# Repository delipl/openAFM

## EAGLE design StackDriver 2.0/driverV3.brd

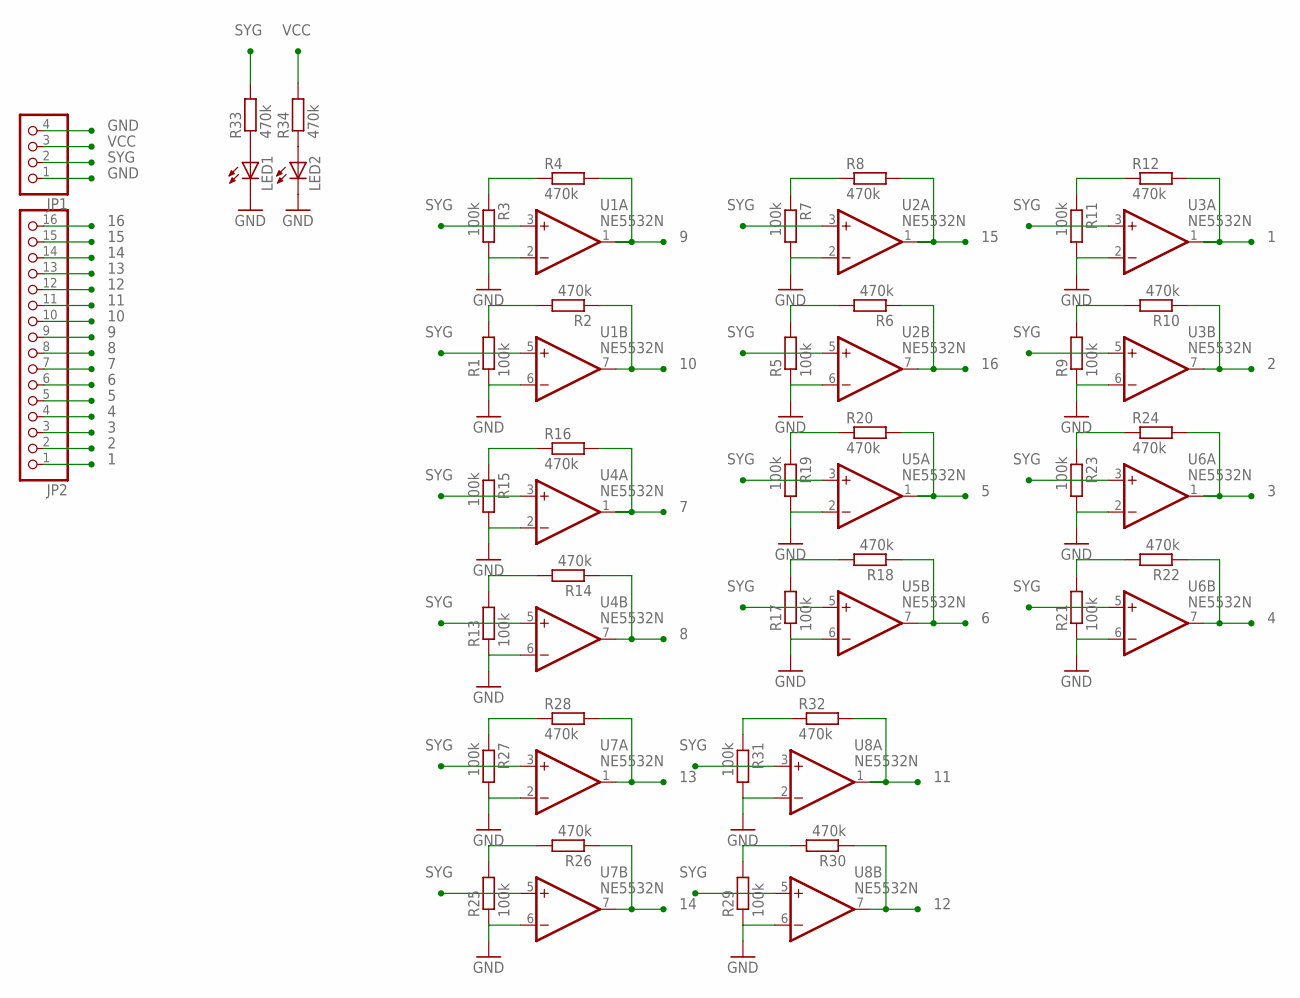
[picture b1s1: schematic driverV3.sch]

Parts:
JP1: PINHD-1X4; 1X04
JP2: PINHD-1X16; 1X16
LED1, LED2: LED_ELD260; LED_LD260
R1, R3, R5, R7, R9, R11, R13, R15, R17, R19, R21, R23, R25, R27, R29, R31: 100k; 0204/7
R2, R4, R6, R8, R10, R12, R14, R16, R18, R20, R22, R24, R26, R28, R30, R32, R33, R34: 470k; 0204/7
U1, U2, U3, U4, U5, U6, U7, U8: NE5532N; DIL08

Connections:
1: JP2.1, R12.2, U3.1 (OUT)
2: JP2.2, R10.1, U3.7 (OUT)
3: JP2.3, R24.2, U6.1 (OUT)
4: JP2.4, R22.1, U6.7 (OUT)
5: JP2.5, R20.2, U5.1 (OUT)
6: JP2.6, R18.1, U5.7 (OUT)
7: JP2.7, R16.2, U4.1 (OUT)
8: JP2.8, R14.1, U4.7 (OUT)
9: JP2.9, R4.2, U1.1 (OUT)
10: JP2.10, R2.1, U1.7 (OUT)
11: JP2.11, R32.2, U8.1 (OUT)
12: JP2.12, R30.1, U8.7 (OUT)
13: JP2.13, R28.2, U7.1 (OUT)
14: JP2.14, R26.1, U7.7 (OUT)
15: JP2.15, R8.2, U2.1 (OUT)
16: JP2.16, R6.1, U2.7 (OUT)
GND: JP1.1, JP1.4, LED1.K (C), LED2.K (C), R1.1, R3.2, R5.1, R7.2, R9.1, R11.2, R13.1, R15.2, R17.1, R19.2, R21.1, R23.2, R25.1, R27.2, R29.1, R31.2, U1.2 (-IN), U1.4 (V-), U1.6 (-IN), U2.2 (-IN), U2.4 (V-), U2.6 (-IN), U3.2 (-IN), U3.4 (V-), U3.6 (-IN), U4.2 (-IN), U4.4 (V-), U4.6 (-IN), U5.2 (-IN), U5.4 (V-), U5.6 (-IN), U6.2 (-IN), U6.4 (V-), U6.6 (-IN), U7.2 (-IN), U7.4 (V-), U7.6 (-IN), U8.2 (-IN), U8.4 (V-), U8.6 (-IN)
unnamed: R5.2, R6.2
unnamed: R1.2, R2.2
unnamed: R7.1, R8.1
unnamed: R9.2, R10.2
unnamed: R3.1, R4.1
unnamed: R11.1, R12.1
unnamed: R13.2, R14.2
unnamed: R15.1, R16.1
unnamed: R17.2, R18.2
unnamed: R19.1, R20.1
unnamed: R21.2, R22.2
unnamed: R23.1, R24.1
unnamed: R25.2, R26.2
unnamed: R27.1, R28.1
unnamed: R29.2, R30.2
unnamed: R31.1, R32.1
unnamed: LED1.A, R33.1
unnamed: LED2.A, R34.1
SYG: JP1.2, R33.2, U1.3 (+IN), U1.5 (+IN), U2.3 (+IN), U2.5 (+IN), U3.3 (+IN), U3.5 (+IN), U4.3 (+IN), U4.5 (+IN), U5.3 (+IN), U5.5 (+IN), U6.3 (+IN), U6.5 (+IN), U7.3 (+IN), U7.5 (+IN), U8.3 (+IN), U8.5 (+IN)
VCC: JP1.3, R34.2, U1.8 (V+), U2.8 (V+), U3.8 (V+), U4.8 (V+), U5.8 (V+), U6.8 (V+), U7.8 (V+), U8.8 (V+)

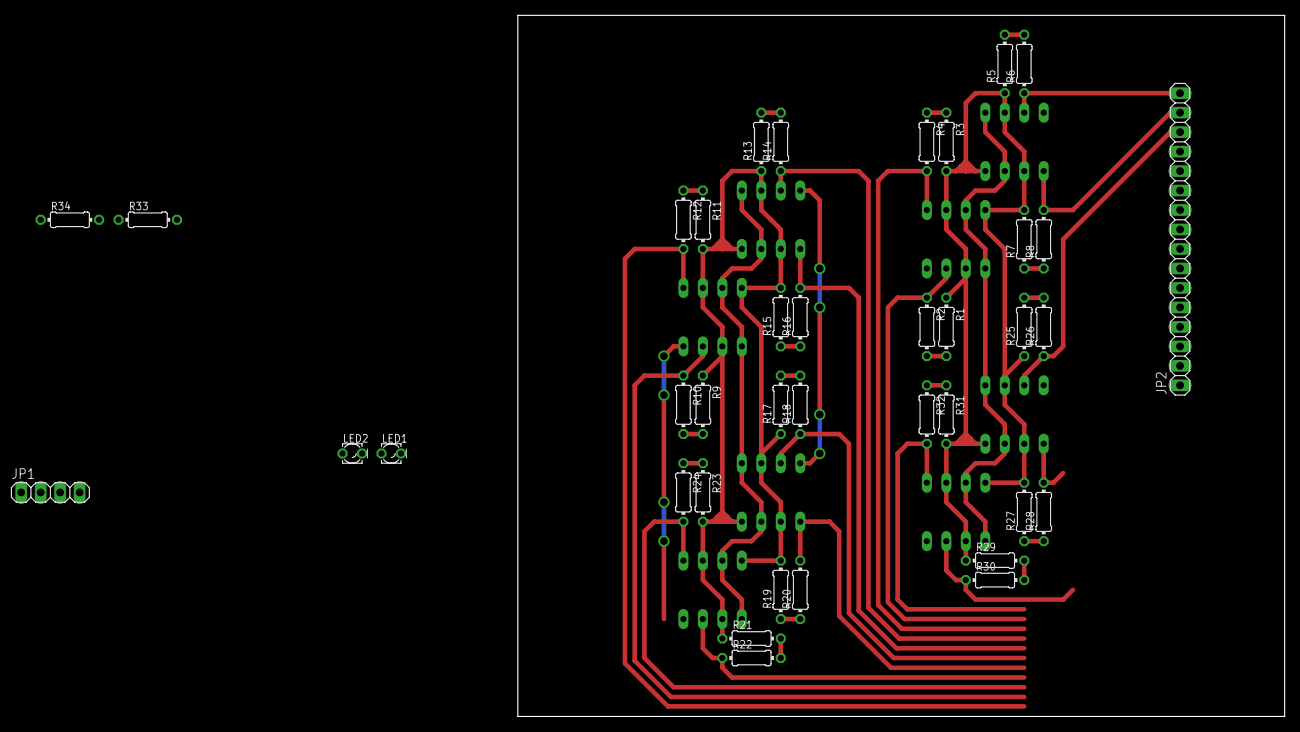
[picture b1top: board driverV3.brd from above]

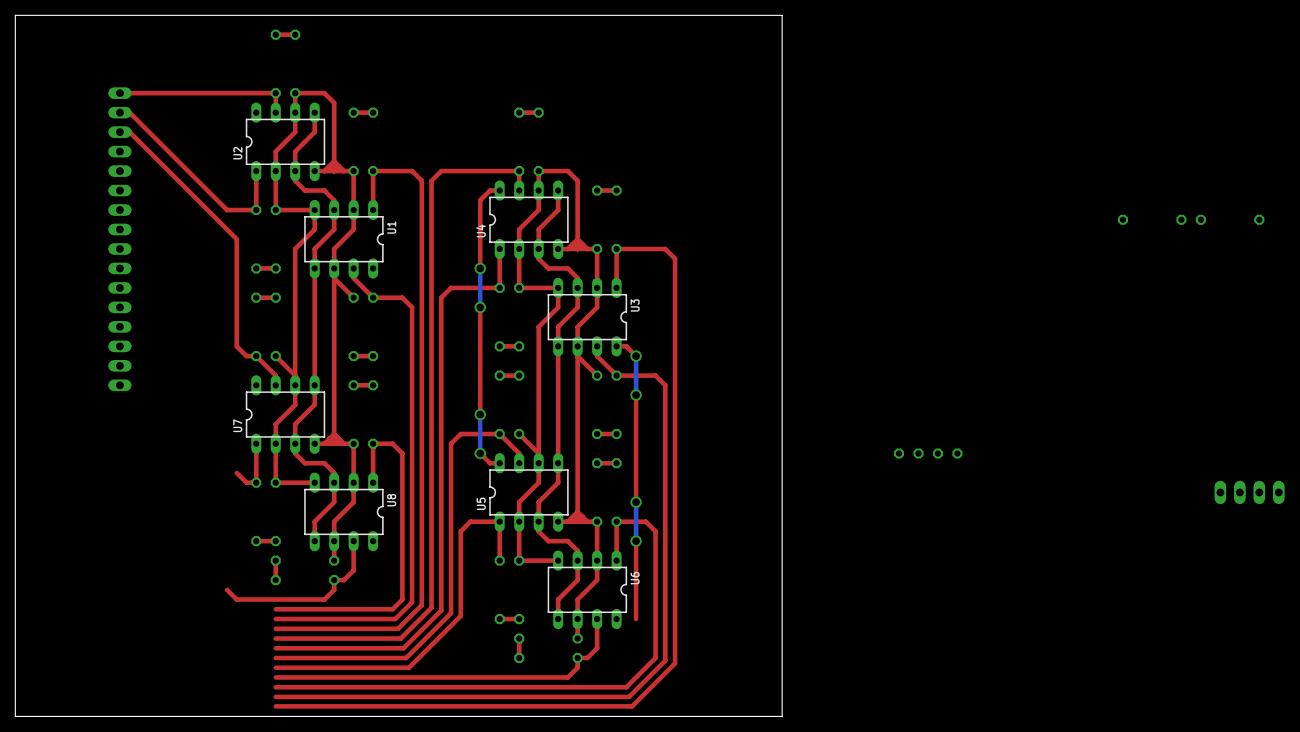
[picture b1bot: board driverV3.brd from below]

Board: 2 copper layers, 100.0 x 91.4 mm, 46 parts (8 on the bottom side), 37 nets.

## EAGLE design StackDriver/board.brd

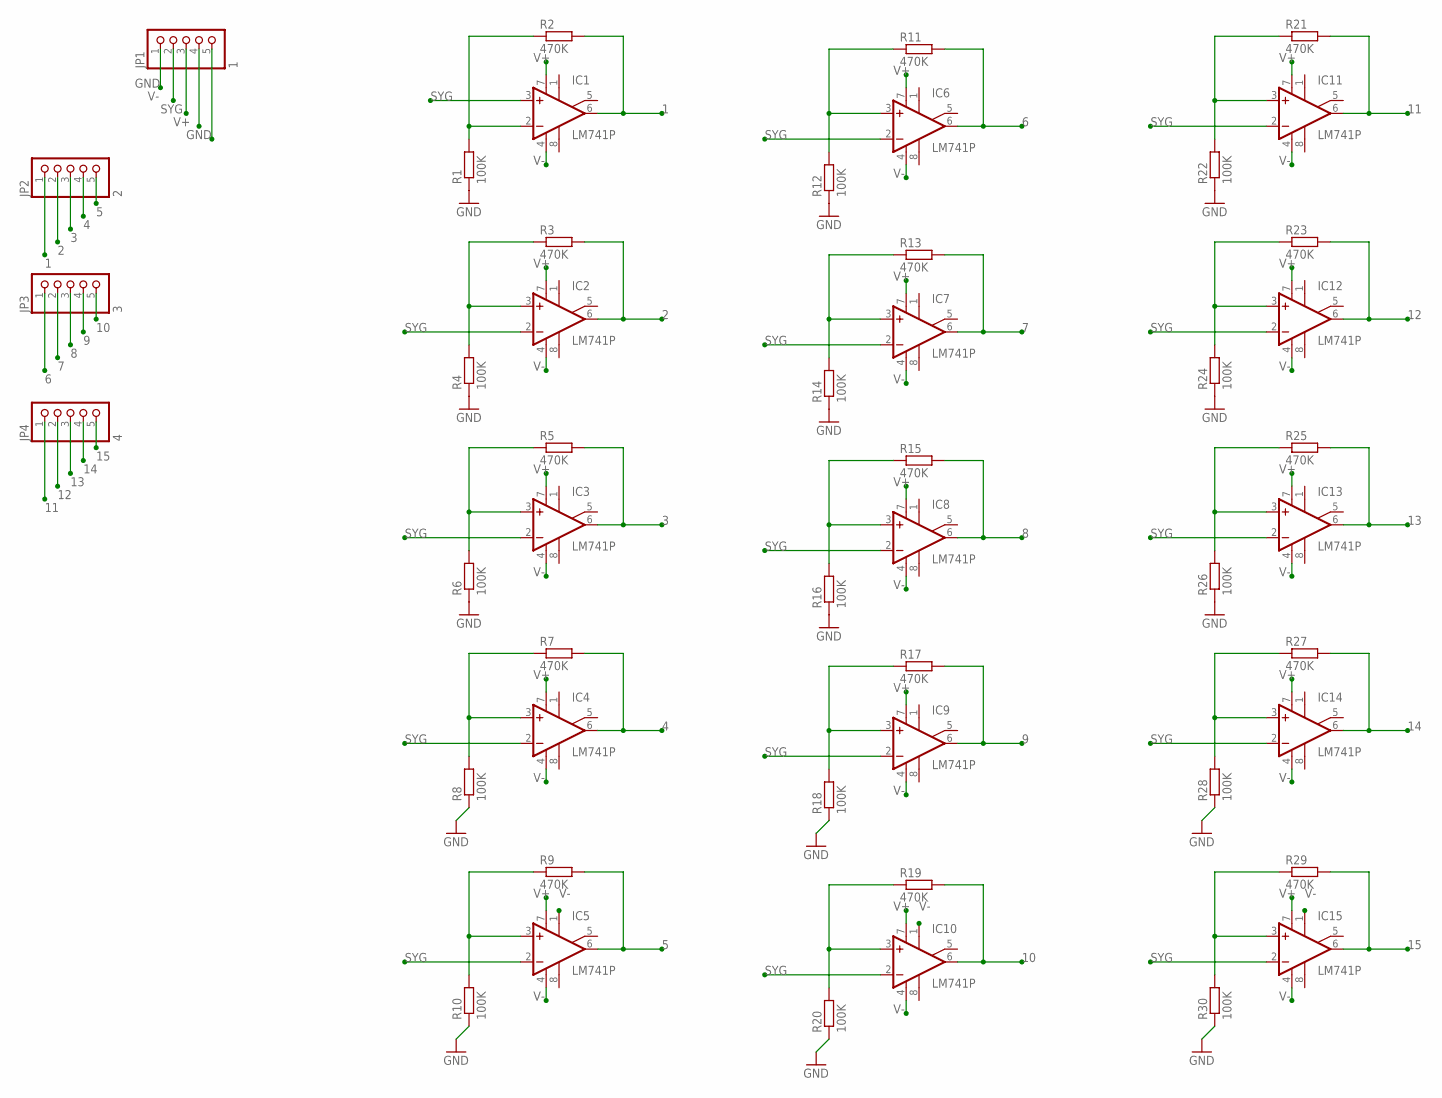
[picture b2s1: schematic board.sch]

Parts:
IC1, IC2, IC3, IC4, IC5, IC6, IC7, IC8, IC9, IC10, IC11, IC12, IC13, IC14, IC15: LM741P; DIL08
JP1: 1; 1X05
JP2: 2; 1X05
JP3: 3; 1X05
JP4: 4; 1X05
R1, R4, R6, R8, R10, R12, R14, R16, R18, R20, R22, R24, R26, R28, R30: 100K; 0204/7
R2, R3, R5, R7, R9, R11, R13, R15, R17, R19, R21, R23, R25, R27, R29: 470K; 0204/7

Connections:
1: IC1.6 (OUT), JP2.1, R2.2
2: IC2.6 (OUT), JP2.2, R3.2
3: IC3.6 (OUT), JP2.3, R5.2
4: IC4.6 (OUT), JP2.4, R7.2
5: IC5.6 (OUT), JP2.5, R9.2
6: IC6.6 (OUT), JP3.1, R11.2
7: IC7.6 (OUT), JP3.2, R13.2
8: IC8.6 (OUT), JP3.3, R15.2
9: IC9.6 (OUT), JP3.4, R17.2
10: IC10.6 (OUT), JP3.5, R19.2
11: IC11.6 (OUT), JP4.1, R21.2
12: IC12.6 (OUT), JP4.2, R23.2
13: IC13.6 (OUT), JP4.3, R25.2
14: IC14.6 (OUT), JP4.4, R27.2
15: IC15.6 (OUT), JP4.5, R29.2
GND: JP1.1, JP1.5, R1.1, R4.1, R6.1, R8.1, R10.1, R12.1, R14.1, R16.1, R18.1, R20.1, R22.1, R24.1, R26.1, R28.1, R30.1
unnamed: IC2.3 (+IN), R3.1, R4.2
unnamed: IC1.2 (-IN), R1.2, R2.1
unnamed: IC3.3 (+IN), R5.1, R6.2
unnamed: IC4.3 (+IN), R7.1, R8.2
unnamed: IC5.3 (+IN), R9.1, R10.2
unnamed: IC6.3 (+IN), R11.1, R12.2
unnamed: IC7.3 (+IN), R13.1, R14.2
unnamed: IC8.3 (+IN), R15.1, R16.2
unnamed: IC9.3 (+IN), R17.1, R18.2
unnamed: IC10.3 (+IN), R19.1, R20.2
unnamed: IC11.3 (+IN), R21.1, R22.2
unnamed: IC12.3 (+IN), R23.1, R24.2
unnamed: IC13.3 (+IN), R25.1, R26.2
unnamed: IC14.3 (+IN), R27.1, R28.2
unnamed: IC15.3 (+IN), R29.1, R30.2
SYG: IC1.3 (+IN), IC2.2 (-IN), IC3.2 (-IN), IC4.2 (-IN), IC5.2 (-IN), IC6.2 (-IN), IC7.2 (-IN), IC8.2 (-IN), IC9.2 (-IN), IC10.2 (-IN), IC11.2 (-IN), IC12.2 (-IN), IC13.2 (-IN), IC14.2 (-IN), IC15.2 (-IN), JP1.3
V+: IC1.7 (V+), IC2.7 (V+), IC3.7 (V+), IC4.7 (V+), IC5.7 (V+), IC6.7 (V+), IC7.7 (V+), IC8.7 (V+), IC9.7 (V+), IC10.7 (V+), IC11.7 (V+), IC12.7 (V+), IC13.7 (V+), IC14.7 (V+), IC15.7 (V+), JP1.4
V-: IC1.4 (V-), IC2.4 (V-), IC3.4 (V-), IC4.4 (V-), IC5.1 (ON1), IC5.4 (V-), IC6.4 (V-), IC7.4 (V-), IC8.4 (V-), IC9.4 (V-), IC10.1 (ON1), IC10.4 (V-), IC11.4 (V-), IC12.4 (V-), IC13.4 (V-), IC14.4 (V-), IC15.1 (ON1), IC15.4 (V-), JP1.2

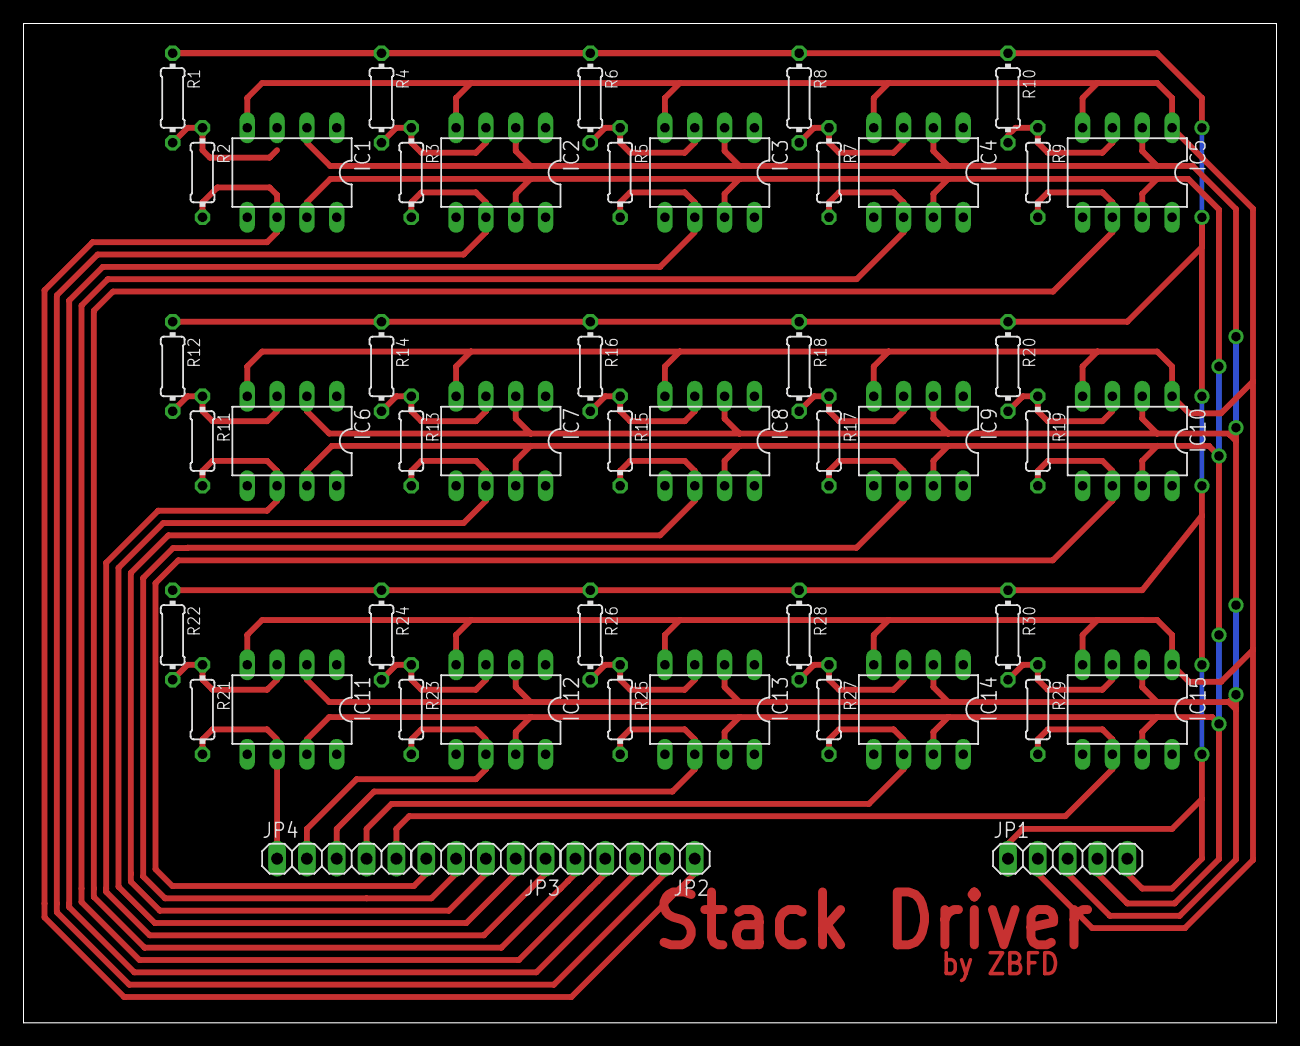
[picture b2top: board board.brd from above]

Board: 2 copper layers, 106.7 x 85.1 mm, 49 parts (0 on the bottom side), 34 nets.

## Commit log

2018-10-17 Nie umiem w płytki. Teraz bedzie gut
2018-10-17 Zrobiony schemat
2018-10-17 chyba działa
2018-10-17 Dodałem schamat

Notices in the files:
parts and their libraries:
op-amp: Copyright (C) 2006 by Bob Starr
